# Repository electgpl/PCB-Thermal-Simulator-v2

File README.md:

# PCB Thermal Simulator v2

Steady-state thermal simulation of a PCB **straight from the KiCad layout**.
It reads the `.kicad_pcb`, rebuilds the real copper of every layer (zones, tracks,
pads, vias), and solves heat conduction across the stack-up with convection and
radiation to ambient. Pure Python, no KiCad installation needed.

## What changed from v1

| | v1 | v2 |
|---|---|---|
| Input | STEP + CSV | `.kicad_pcb` (+ CSV or KiCad fields) |
| Copper | one global "fill factor" | real copper per layer, rasterized from the layout |
| Stack-up | single lumped layer | one node plane per copper layer, coupled through FR4 and via barrels |
| Stack-up data | typed in `config.py` | read from Board Setup → Physical Stackup |
| Heat entry | component bounding box | component pads (exposed pad detected automatically) |
| Cooling | fixed `h` | natural-convection correlation + radiation, or fixed `h` |
| Tj | `T_pcb + P·θJC` | `T_pads + P·θJB` |
| Result | temperatures only | PASS / MARGINAL / FAIL per component against its temperature limit |
| Checks | none | analytical validation tests, energy balance |

The STEP parser is gone: the STEP file only gave component boxes, and the layout
already has them (plus everything else).

## Quick start

### From Thonny (or IDLE, VS Code…)

1. Install the packages: *Tools → Manage packages…* → `numpy`, `scipy`, `matplotlib`, `Pillow`.
2. Open `main.py`, edit the `CONFIGURACIÓN` block at the top (board file, CSV,
   ambient temperature, …) and press **Run (F5)**.

The results print in the Shell, the image opens in a window, and the files are
saved in `thermal_out/` next to `main.py`. Set `MAKE_TEMPLATE = True` once to
get a CSV listing every component, ready to fill in.

### From the command line

```bash
pip install -r requirements.txt

# 1. Get a CSV listing every component, fill in the Power_W column
python main.py board.kicad_pcb --template powers.csv

# 2. Simulate
python main.py board.kicad_pcb --csv powers.csv

# Included example (AP64501 buck, 4 layers)
python main.py examples/EMI_SS_Supply_Electgpl.kicad_pcb --csv examples/EMI_SS_Supply_Electgpl.csv
```

**Fill the zones (`B`) and save the board before running.** The simulator uses
the filled copper stored in the file; unfilled zones are reported and ignored.

Outputs go to `thermal_out/`:

| File | Contents |
|---|---|
| `thermal_map.png` | Verdict banner, top and bottom temperature maps, per-component table |
| `copper_layers.png` | The copper and vias exactly as the solver sees them (sanity check) |
| `report.csv` | Per component: power, pad temperature, Tj, limit, margin, status |
| `temperature.npz` | Full temperature field `T[layer, y, x]` for post-processing |

### Options

| Option | Default | Meaning |
|---|---|---|
| `--cell` | 0.2 | Cell size in mm. Keep it at or below half your copper clearance |
| `--T_amb` | 25 | Ambient temperature, °C |
| `--orientation` | horizontal | `horizontal` or `vertical` board, for natural convection |
| `--h` | – | Fixed convective coefficient on both faces, W/m²K (forced air: 20–60) |
| `--emissivity` | 0.9 | Surface emissivity; 0 disables radiation |
| `--margin` | 10 | Minimum margin to the limit, °C, to call it a pass |
| `--limit` | – | Temperature limit for components that do not have their own `T_max` |
| `--plating` | 25 | Via barrel plating, µm |
| `--k_fr4_xy`, `--k_fr4_z` | 0.8, 0.3 | FR4 conductivity in-plane / through-plane, W/m·K |

## Giving it the power data

Two sources, merged per component (the CSV wins):

**1. KiCad fields.** Add fields to the schematic symbols and run *Update PCB from
Schematic*. Then no CSV is needed and the data lives with the design.

**2. CSV.**

```csv
Component,Power_W,T_max,Theta_JB,Theta_JC,Theta_JA,Thermal_Pads,Description
U1,1.0,125,,5,45,,AP64501SP-13
L1,0.2,125,,,,,IHLP-4040
```

| Field | Required | Meaning |
|---|---|---|
| `Power_W` | yes | Dissipated power, W |
| `T_max` | no | Maximum allowed temperature, °C: Tj max for ICs, max operating temperature for passives. Needed for the pass/fail verdict |
| `Theta_JB` | no | Junction-to-board (or ΨJB), °C/W. Used for Tj |
| `Theta_JC` | no | Used as θJB if `Theta_JB` is missing. Only correct when it is junction-to-case **bottom** (exposed-pad packages) |
| `Theta_JA` | no | Not used by the solver; reported as the datasheet estimate for comparison |
| `Thermal_Pads` | no | Pad numbers that carry the heat, e.g. `9` or `2 4` |

Where the heat enters the board: the pads in `Thermal_Pads`; otherwise the
exposed pad or tab (TO-252, SOT-223…) if the footprint has one; otherwise all
pads, weighted by area. Lines starting with `#` in the CSV are comments.

## Pass / fail

Give each component its limit (`T_max`) and the run ends with a verdict:

```
>>> PASA — peor caso U1: Tj 90 °C, límite 125 °C (margen 35 °C; aguanta hasta ~60 °C de ambiente)
```

| Status | Meaning |
|---|---|
| `PASA` | margin to the limit ≥ `--margin` (10 °C by default) |
| `JUSTO` | within the limit, but with less margin than that |
| `FALLA` | over the limit |

- The limit is compared against **Tj** when a θJB/θJC is available, otherwise
  against the simulated **pad temperature** (fine for small passives; a part
  with internal losses, like an inductor, runs hotter inside than at its pads).
- "Amb. máx" is the ambient temperature at which the component would reach its
  limit, estimated as `T_amb + margin`. It errs on the safe side (on the example
  board, re-running at that ambient gives about 5 °C less than the limit).
- The process exit code is 1 on `FALLA`, so it can gate a CI job.
- Components without `T_max` are listed as "sin límite" and do not count.

## Who heats whom

All heat sources are solved together on the same board, so every component
sees its own heating plus what its neighbours add through the copper. The run
prints the split, and `report.csv` has it as `Rise_own_C` / `Rise_from_neighbours_C`:

```
U1    pads a +59.6 °C = 46.2 propio + 6.5 de L1 + 5.7 de L2 + 1.1 de otros
L1    pads a +50.3 °C = 9.5 propio + 32.7 de U1 + 6.9 de L2 + 1.2 de otros
```

## Model

One 2D grid per copper layer; one temperature node per cell per layer.

- **In-plane:** sheet conductance `S = k_cu·t_cu·f + k_fr4·t_fr4` where `f` is the
  real copper fraction of the cell. Neighbour cells are linked by the harmonic
  mean of `S`, so a clearance gap or an isolated island blocks heat as it should.
- **Between layers:** `k_fr4_z·A/d` through the dielectric, plus the barrel of
  every via or through-hole pad in the cell, `k_cu·π·t_p·(d_drill − t_p)/d`.
- **To ambient (top and bottom faces):** `h_conv + h_rad`.
  `h_conv` from flat-plate natural-convection correlations (Incropera ch. 9:
  `Nu = 0.54·Ra^¼` facing up, `0.27·Ra^¼` facing down, `0.59·Ra^¼` vertical),
  using the mean face temperature. `h_rad = ε·σ·(T² + T_amb²)·(T + T_amb)` per cell.
- Since `h` depends on `T`, the sparse linear system is solved a few times
  (factorized once, then preconditioned CG) until the temperature settles.
- **Junction:** `Tj = T_pads + P·θJB`, with `T_pads` the simulated mean
  temperature of the pads that carry the heat.

## Validation

`python -m pytest tests` (or `python tests/test_validation.py`):

- uniform heating of a plate: matches `T_amb + P/(2hA)` exactly
- point source on a large copper sheet with convection: within 2 % of the
  analytical `P/(2πkt)·K0(r/L)` solution
- two layers through FR4: inter-layer drop matches `q·d/k_z`
- a copper gap isolates the two sides
- KiCad loader: stack-up, outline, via count, pad rotations checked on the example
- energy balance: power in = power out

Mesh check on the example board: hottest point 84.2 / 85.7 / 86.0 °C at
0.4 / 0.2 / 0.1 mm cells.

**Not yet compared against a thermal camera.** The physics is checked against
theory; the absolute numbers on a real board depend mostly on the convection
estimate (expect ±20–30 %) and on the power you enter.

## Limitations

- Air is not simulated (no CFD): enclosures, nearby boards, or airflow shadows are
  only as good as the `h` you give.
- All component power goes into the board; heat leaving through the package body
  is ignored (conservative). Tall parts like inductors run cooler in reality.
- No Joule heating in tracks, no transient.
- Blind/buried vias are supported; back-drilled or tented/filled via differences are not.
- Board cut-outs are handled; drill holes do not remove material.

## Architecture

```
kicad_loader.py   .kicad_pcb  ─┐
(future) gerber / IPC-2581 ────┼─►  board_model.Board  ─►  rasterizer.Grid  ─►  thermal_solver
                               ┘         ▲                                            │
power.py  (KiCad fields + CSV) ──────────┘                          renderer / report ◄┘
```

`Board` is EDA-independent (outline, stack-up, copper shapes per layer, vias,
components with pads). Supporting another EDA means writing one loader that
returns a `Board`; nothing else changes.

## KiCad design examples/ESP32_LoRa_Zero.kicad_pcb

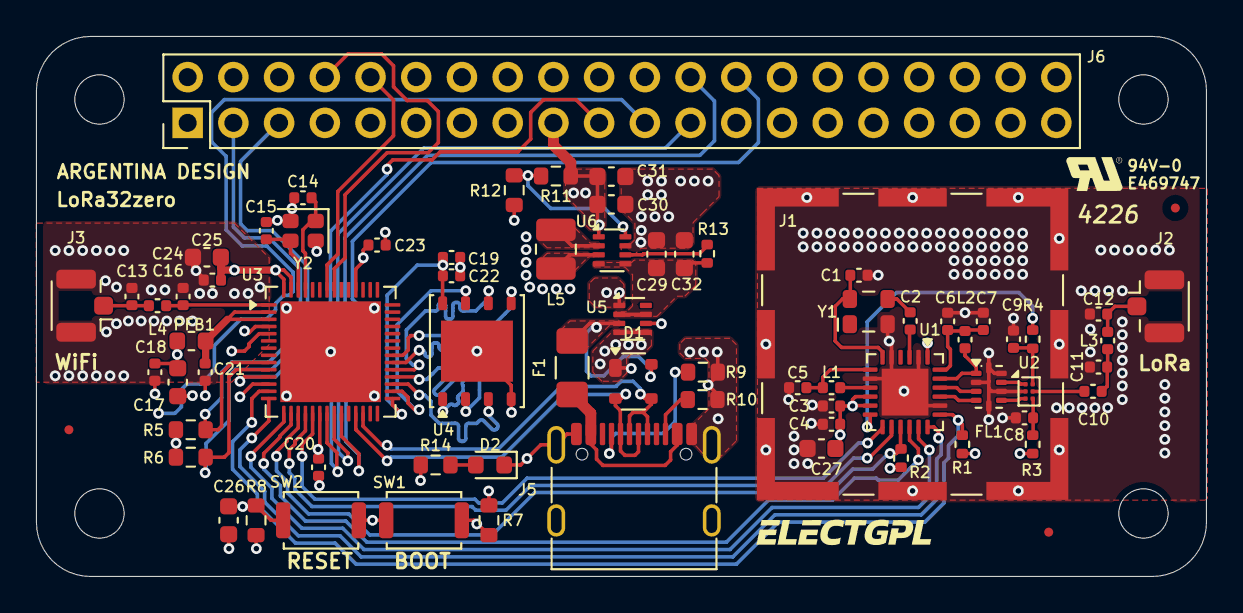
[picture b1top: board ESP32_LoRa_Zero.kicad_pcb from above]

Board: 4 copper layers, 65.0 x 30.0 mm, 73 parts (0 on the bottom side), 62 nets.

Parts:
C1, C4, C18, C20, C21, C22, C23, C24: 100nF; C_0402_1005Metric
C2: 10nF; C_0402_1005Metric
C3, C19: 1uF; C_0402_1005Metric
C5: 470nF; C_0402_1005Metric
C6: 47pF; C_0402_1005Metric
C7: 47nF; C_0402_1005Metric
C8, C9: 1nF; C_0402_1005Metric
C10: 39pF; C_0402_1005Metric
C11, C12, C14, C15, C16: 10pF; C_0402_1005Metric
C13: 0.85pF; C_0402_1005Metric
C17, C25, C26, C27: 10uF; C_0603_1608Metric
C29, C30, C31, C32: 22uF; C_0603_1608Metric
D1: BST143A053U; SOT-143
D2: LED; LED_0603_1608Metric
F1: nSMD150; Fuse_1206_3216Metric_Pad1.42x1.75mm_HandSolder
FID1, FID2, FID3: Fiducial; Fiducial_0.5mm_Mask1.5mm
FL1: IPD915; Balun_Johanson_0900FM15K0039
J1: RFShield_TwoPieces; Laird_Technologies_BMI-S-202-F_16.50x16.50mm
J2, J3: U.FL; U.FL_Hirose_U.FL-R-SMT-1_Vertical
J5: USB_C_Receptacle_USB2.0_16P; USB_C_Receptacle_G-Switch_GT-USB-7010ASV
J6: Raspberry_Pi_Zero_Conn_02x20_Odd_Even; Raspberry_Pi_Zero
L1: 15uH; C_0402_1005Metric
L2: 47nH; C_0402_1005Metric
L3: 000; C_0402_1005Metric
L4: 0.84nH; C_0402_1005Metric
L5: 1uH; L_1008_2520Metric
PFB1: 330R; L_0603_1608Metric
R1, R2, R13: 10k; R_0402_1005Metric
R3, R4: 100R; R_0402_1005Metric
R5, R6, R14: 1k8; R_0603_1608Metric
R7, R8: 10k; R_0603_1608Metric
R9, R10: 5k1; R_0603_1608Metric
R11: 511k; R_0603_1608Metric
R12: 91k; R_0603_1608Metric
SW1, SW2: SW_Push; SW_Push_SPST_NO_Alps_SKRK
U1: SX1262IMLTRT; QFN-24-1EP_4x4mm_P0.5mm_EP2.6x2.6mm
U2: BGS12WN6E6327; Infineon_PG-TSNP-6-10_0.7x1.1mm_0.7x1.1mm_P0.4mm
U3: ESP32-S3; QFN-56-1EP_7x7mm_P0.4mm_EP5.6x5.6mm
U4: GD25Q128EWIGY; WSON-8-1EP_6x5mm_P1.27mm_EP3.4x4mm
U5: LM66200; SOT-583-8
U6: TPS631000; SOT-583-8
Y1: X1G0054210205; Oscillator_SMD_SeikoEpson_TG2520SMN-xxx-xxxxxx-4Pin_2.5x2.0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
Y2: R940000096; Crystal_SMD_2016-4Pin_2.0x1.6mm

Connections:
+3.3V: C3.1, C4.1, C17.1, C18.1, C20.1, C23.1, C24.1, C25.1, C27.1, C30.2, C31.2, J6.1, J6.17, PFB1.2, R1.1, R2.1, R3.1, R5.1, R6.1, R7.1, R8.1, R11.1, R14.1, U1.1 (VDD_IN), U1.10 (VBAT), U1.11 (VBAT_IO), U3.20 (VDD3P3_RTC), U3.46 (VDD3P3_CPU), U3.55 (VDDA), U3.56 (VDDA), U6.1 (VOUT)
/CONN-2x20+USBC/5V: J6.2, J6.4, U5.6 (VIN2)
/CONN-2x20+USBC/D_N: D1.2 (I/O1), J5.A7 (D-), J5.B7 (D-), U3.25 (GPIO19/USB_D-/ADC2_CH8)
/CONN-2x20+USBC/D_P: D1.3 (I/O2), J5.A6 (D+), J5.B6 (D+), U3.26 (GPIO20/USB_D+/ADC2_CH9)
/CONN-2x20+USBC/GPIO2/SDA: J6.3, R5.2, U3.9 (GPIO4/ADC1_CH3)
/CONN-2x20+USBC/GPIO3/SCL: J6.5, R6.2, U3.10 (GPIO5/ADC1_CH4)
/CONN-2x20+USBC/GPIO7/CE1: J6.26, U3.23 (GPIO17/ADC2_CH6)
/CONN-2x20+USBC/GPIO8/CE0: J6.24, U3.22 (GPIO16/ADC2_CH5/XTAL_32K_N)
/CONN-2x20+USBC/GPIO9/MISO: J6.21, U3.12 (GPIO7/ADC1_CH6)
/CONN-2x20+USBC/GPIO10/MOSI: J6.19, U3.11 (GPIO6/ADC1_CH5)
/CONN-2x20+USBC/GPIO11/SCLK: J6.23, U3.21 (GPIO15/ADC2_CH4/XTAL_32K_P)
/CONN-2x20+USBC/GPIO14/TX: J6.8, U3.49 (U0TXD/PROG/GPIO43)
/CONN-2x20+USBC/GPIO15/RX: J6.10, U3.50 (U0RXD/PROG/GPIO44)
/LORA-SX1262/SX_BUSY: U1.14 (BUSY), U3.18 (GPIO13/ADC2_CH2)
/LORA-SX1262/SX_DIO1: U1.13 (DIO1), U3.19 (GPIO14/ADC2_CH3)
/LORA-SX1262/SX_MISO: U1.16 (MISO), U3.16 (GPIO11/ADC2_CH0)
/LORA-SX1262/SX_MOSI: U1.17 (MOSI), U3.15 (GPIO10/ADC1_CH9)
/LORA-SX1262/SX_NRESET: R2.2, U1.15 (~RESET), U3.17 (GPIO12/ADC2_CH1)
/LORA-SX1262/SX_NSS: R1.2, U1.19 (NSS), U3.13 (GPIO8/ADC1_CH7)
/LORA-SX1262/SX_SCK: U1.18 (SCK), U3.14 (GPIO9/ADC1_CH8)
ANT_SW_CTRL: R4.2, U1.12 (DIO2)
BOOT: R7.2, SW1.2, U3.5 (GPIO0/BOOT)
CHIP_PU: C26.1, R8.2, SW2.2, U3.4 (CHIP_PU/RESET)
GND: C1.2, C3.2, C4.2, C5.1, C6.2, C7.2, C8.2, C9.2, C11.2, C12.2, C13.2, C14.2, C15.2, C16.2, C17.2, C18.2, C19.2, C20.2, C21.2, C22.2, C23.2, C24.2, C25.2, C26.2, C27.2, C29.1, C30.1, C31.1, C32.1, D1.1 (GND), D2.1 (K), FL1.2 (GND), FL1.5 (GND), FL1.7 (GND), FL1.9 (GND), FL1.10 (GND), J1.1 (Shield_1), J2.2 (Ext), J3.2 (Ext), J5.A1 (GND), J5.A12 (GND), J5.B1 (GND), J5.B12 (GND), J5.SH, J6.6, J6.9, J6.14, J6.20, J6.25, J6.30, J6.34, J6.39, R9.1, R10.1, R12.2, SW1.1, SW2.1, U1.2 (GND), U1.5 (GND), U1.8 (GND), U1.20 (GND), U1.25 (GND), U2.2 (GND), U3.57 (GND), U4.4 (GND), U4.9 (PAD), U5.1 (GND), U5.4 (~ON), U5.5 (GND), U6.7 (GND), Y1.2 (GND), Y2.2, Y2.4
unnamed: C10.2, C11.1, L3.1
unnamed: D2.2 (A), R14.2
unnamed: F1.1, J5.A4 (VBUS), J5.A9 (VBUS), J5.B4 (VBUS), J5.B9 (VBUS)
unnamed: FL1.3 (RFI_N), U1.22 (RFI_N)
unnamed: FL1.4 (RFI_P), U1.21 (RFI_P)
unnamed: FL1.1 (RFO), L2.2, U1.23 (RFO)
unnamed: FL1.6 (SW_RFI), U2.3 (RF1)
unnamed: FL1.8 (SW_RFO), U2.1 (RF2)
unnamed: C12.1, J2.1 (In), L3.2
unnamed: C13.1, J3.1 (In), L4.2
unnamed: J5.A5 (CC1), R9.2
unnamed: J5.B5 (CC2), R10.2
unnamed: L1.2, U1.9 (DCC_SW)
unnamed: C5.2, L1.1, U1.7 (VREG)
unnamed: C6.1, C7.1, L2.1, U1.24 (VR_PA)
unnamed: C9.1, R4.1, U2.6 (CTRL)
unnamed: C10.1, U2.5 (RFIN)
unnamed: C8.1, R3.2, U2.4 (VDD)
unnamed: C16.1, L4.1, U3.1 (LNA_IN/RF)
unnamed: C14.1, U3.53 (XTAL_N), Y2.1
unnamed: C15.1, U3.54 (XTAL_P), Y2.3
unnamed: C29.2, C32.2, R13.1, U5.2 (VOUT), U5.7 (VOUT), U6.4 (VIN), U6.5 (EN)
unnamed: R11.2, R12.1, U6.8 (FB)
unnamed: L5.1, U6.3 (LX1)
unnamed: L5.2, U6.2 (LX2)
unnamed: R13.2, U6.6 (MODE)
unnamed: C2.1, Y1.3 (OUT)
SPICLK: U3.33 (SPICLK/GPIO30), U4.6 (CLK)
SPICS0: U3.32 (SPICS0/GPIO29), U4.1 (~CS)
SPID: U3.35 (SPID/GPIO32), U4.5 (DI)
SPIHD: U3.30 (SPIHD/GPIO27), U4.7 (~RESET)
SPIQ: U3.34 (SPIQ/GPIO31), U4.2 (DO)
SPIWP: U3.31 (SPIWP/GPIO28), U4.3 (~WP)
SX_DIO3: C1.1, U1.6 (DIO3), Y1.4 (Vcc)
TXCO: C2.2, U1.3 (XTA)
VDD3P3: C21.1, PFB1.1, U3.2 (VDD3P3), U3.3 (VDD3P3)
VDD_SPI: C19.1, C22.1, U3.29 (VDD_SPI), U4.8 (VCC)
VUSB: D1.4 (VCC), F1.2, U5.3 (VIN1)

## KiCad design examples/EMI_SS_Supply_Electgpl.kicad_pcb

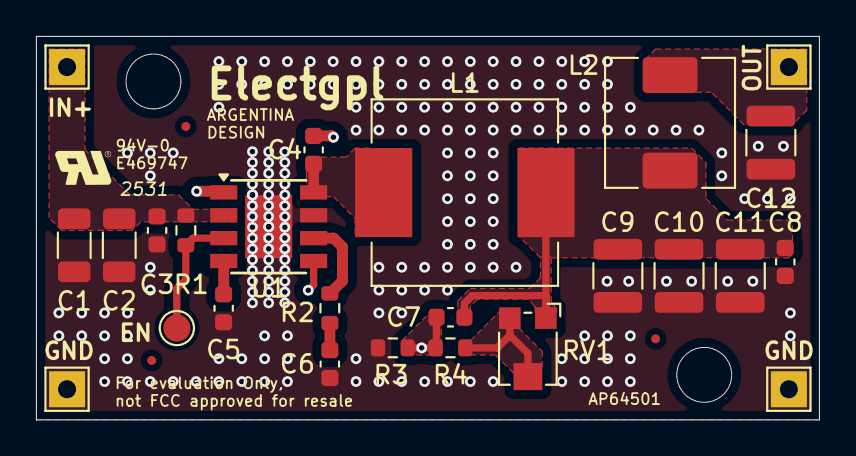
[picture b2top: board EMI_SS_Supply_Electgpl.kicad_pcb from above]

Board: 4 copper layers, 43.5 x 21.3 mm, 28 parts (0 on the bottom side), 12 nets.

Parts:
C1, C2: 10µF; C_1206_3216Metric
C3, C4, C8: 100nF; C_0603_1608Metric
C5, C7: 10nF; C_0603_1608Metric
C6: 2.7nF; C_0603_1608Metric
C9, C10, C11, C12: 22µF; C_1210_3225Metric
FID1, FID2, FID3: Fiducial; Fiducial_0.5mm_Mask1mm
L1: 3.6µH; L_Vishay_IHLP-4040
L2: 10µH; L_Wuerth_HCM-7050
R1: 100kΩ; R_0603_1608Metric
R2: 15.8kΩ; R_0603_1608Metric
R3: 2.2kΩ; R_0603_1608Metric
R4: 100Ω; R_0603_1608Metric
RV1: 47kΩ; Potentiometer_Bourns_TC33X_Vertical
TP1, TP2, TP3, TP4: TestPoint; TestPoint_THTPad_2.0x2.0mm_Drill1.0mm
TP5: TestPoint; TestPoint_Pad_D1.5mm
U1: AP64501SP-13; Diodes_SO-8EP

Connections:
GND: C1.2, C2.2, C3.2, C5.2, C6.2, C8.2, C9.2, C10.2, C11.2, C12.2, R3.2, TP2.1, TP4.1, U1.7 (GND), U1.9 (EP)
unnamed: C6.1, R2.2
unnamed: C7.2, C8.1, C9.1, C10.1, C11.1, L1.2, L2.1, RV1.1
unnamed: C12.1, L2.2, TP3.1
unnamed: R4.2, RV1.2, RV1.3
unnamed: C4.1, U1.1 (BST)
unnamed: R2.1, U1.6 (COMP)
unnamed: R1.2, TP5.1, U1.3 (EN)
unnamed: C7.1, R3.1, R4.1, U1.5 (FB)
unnamed: C5.1, U1.4 (SS)
unnamed: C4.2, L1.1, U1.8 (SW)
unnamed: C1.1, C2.1, C3.1, R1.1, TP1.1, U1.2 (VIN)

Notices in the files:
parts and their libraries:
License: MIT - Copyright 2018 StudioPieters®
